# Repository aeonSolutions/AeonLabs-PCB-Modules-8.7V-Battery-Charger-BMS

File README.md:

# AeonLabs-PCB-Modules-8.7V-Battery-Charger-BMS
This is a pcb design module for a  8.7V Battery Charger BMS up to 2A , overcharging, overcurrent protection. Suitable as a add-on design for any other KiCad project.

*Don't forget to LIKE , SHARE and subscribe the free whatsApp group* and if you liked this PCB consider buying me a cup of coffee. Links below.

### Status
  Waiting for first batch from factory. Not tested.

If you already tested this PCB send me a message. Thank you

## Revisions
- revision 1.0
 
## Download options
Download this repository if you need the KiCad Files or, download the Gerber files in the release section of this repository

## Liked it ? Get a Free PCB for yourself
Send me your Device or hardware and i will design a custom PCB for it. Free of charge. Contact-me on WhatsApp or email for more info. 

## Q&A WhatsApp Group
If you have any Questions or simply  like this kind of projects and want to stay updated with the latest research ideas and prototypes during the day and week, join the WhatsApp Group
[A.I. Things](https://chat.whatsapp.com/FkNC7u83kuy2QRA5sqjBVg)

## Fully assembled PCB
Alternatively, and if you do not want to build a PCB by yourself and like to buy one, you can do it here:

The price will be around 30eur plus postage fees.
(I will also deliver the assembled PCB with all the components in place at a fair aditonal cost).

This PCB is a #direct fit #replacement of the one found on the internet at sale. For example here: https://s.click.aliexpress.com/e/_9wRPxz

#### Be supportive of my dedication and work towards technology education and buy me a coffee. Link below.

________________________________________________________________________________________________________________

## PCB Parts list
- [Capacitor SMD 0805](https://s.click.aliexpress.com/e/_AVdmzr)
- [Resistor SMD 1206 ](https://s.click.aliexpress.com/e/_A7OXrR)
- [QFN16 SY6982E](https://s.click.aliexpress.com/e/_DmTDfkf)

## Firmware Download 
one can use the PCB in the repository [AeonLabs-MCU-Burner-USB-to-UART-TTL](https://github.com/aeonSolutions/AeonLabs-MCU-Burner-USB-to-UART-TTL) to program the ESP32 WROOM32 MCU on this PCB.

______________________________________________________________________________________________________________________________

### License
2022 Creative Commons Attribution-NonCommercial-ShareAlike 4.0 International

https://creativecommons.org/licenses/by-nc-sa/4.0/

### Own a copy of this work
if you like to own a copy of this work, you can buy it as a NFT or Ethereum. contact me for more details at mtpsilva@gmail.com
________________________________________________________________________________________________________________
## [Go back to main catalogue page](https://github.com/aeonSolutions/PCB-Prototyping-Catalogue)
________________________________________________________________________________________________________________

### Share this PCB board files

### PCB Fabrication

______________________________________________________________________________________________________________________________

### Be supportive of my dedication and work towards technology education and buy me a cup of coffee
Buy me a cup of coffee, a slice of pizza or a book to help me study, eat and think new PCB design files.

### Make a donation on Paypal
Make a donation on paypal and get a TAX refund*.

### Support all these open hardware projects and become a patreon  
I will give a free PCB design in KiCad to all patreon supporters. To learn more go to patreon.com. Link below.

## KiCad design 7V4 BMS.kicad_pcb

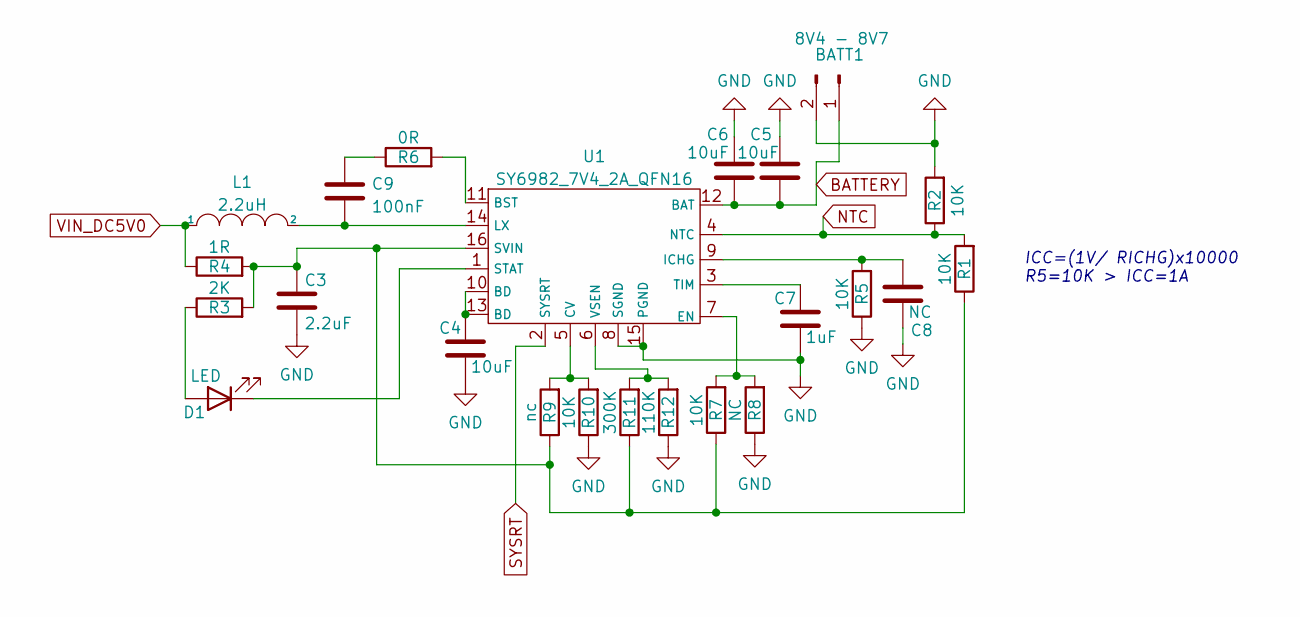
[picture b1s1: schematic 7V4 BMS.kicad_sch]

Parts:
BATT1: 8V4 - 8V7; JST_EH_S2B-EH_1x02_P2.50mm_Horizontal
C3: 2.2uF; C_0805_2012Metric
C4, C5, C6: 10uF; C_0805_2012Metric
C7: 1uF; C_0805_2012Metric
C8: NC; C_0805_2012Metric
C9: 100nF; C_0805_2012Metric
D1: LED; LED_1206_3216Metric
L1: 2.2uH; L_1812_4532Metric
R1, R2, R5, R7, R10: 10K; R_0805_2012Metric
R3: 2K; R_0805_2012Metric
R4: 1R; R_0805_2012Metric
R6: 0R; R_0805_2012Metric
R8: NC; R_0805_2012Metric
R9: nc; R_0805_2012Metric
R11: 300K; R_0805_2012Metric
R12: 110K; R_0805_2012Metric
U1: SY6982_7V4_2A_QFN16; SY6982E 7.4V 2A QFN3x3-16

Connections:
BATTERY: BATT1.1, C5.1, C6.1, U1.12 (BAT)
GND: BATT1.2, C3.2, C4.2, C5.2, C6.2, C7.2, C8.2, R2.2, R5.1, R8.1, R10.1, R12.1, U1.8 (SGND), U1.15 (PGND)
NTC: R1.2, R2.1, U1.4 (NTC)
unnamed: D1.2 (A), R3.1
unnamed: C9.1, R6.1
unnamed: D1.1 (K), U1.1 (STAT)
unnamed: C7.1, U1.3 (TIM)
unnamed: R9.2, R10.2, U1.5 (CV)
unnamed: R11.2, R12.2, U1.6 (VSEN)
unnamed: R7.2, R8.2, U1.7 (EN)
unnamed: C8.1, R5.2, U1.9 (ICHG)
unnamed: C4.1, U1.10 (BD), U1.13 (BD)
unnamed: R6.2, U1.11 (BST)
unnamed: C9.2, L1.2, U1.14 (LX)
unnamed: C3.1, R1.1, R3.2, R4.2, R7.1, R9.1, R11.1, U1.16 (SVIN)
SYSRT: U1.2 (SYSRT)
VIN_DC5V0: L1.1, R4.1

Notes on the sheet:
ICC=(1V/ RICHG)x10000 R5=10K > ICC=1A

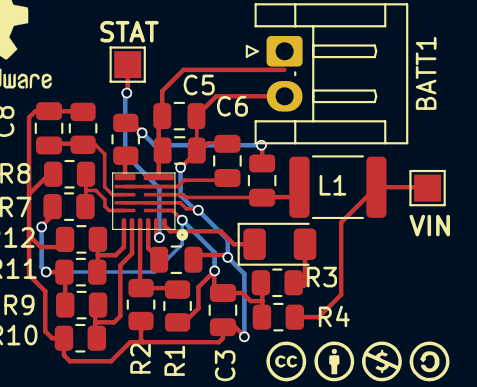
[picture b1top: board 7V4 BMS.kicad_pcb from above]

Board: 2 copper layers, 23 parts (0 on the bottom side), 16 nets.

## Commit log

2022-07-14 rev. 1.0
